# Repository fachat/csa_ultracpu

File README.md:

# Ultra-CPU

Note: this is a part of a larger set of repositories, with [upet_family](https://github.com/fachat/upet_family) as the main repository.

This is the CPU board for a re-incarnation of the Commodore PET or other computer(s) from the later 1970s.

It is build on a Eurocard board and has only parts that can still be obtained new in 2024.
It uses the [CS/A bus interface](http://www.6502.org/users/andre/csa/index.html) to use other I/O boards.

As the memory mapping is programmable using the FPGA on the board, multiple types of computers can
potentially re-created. I started with my favourite one, the Commodore PET.

The reason this board is called Ultra-CPU is because it can potentially be used to recreate not only the Commodore PET.
The downside compared to the Micro-PET is, that it needs a separate I/O board to re-create a Commodore PET.
This can be found [here on my CS/A page](http://www.6502.org/users/andre/csa/petio/index.html).

## Features

The board is built with a number of features:

- Commodore 3032 / 4032 / 8032 / 8296 with options menu to select at boot
  - Boot-menu to select different PET versions to run (BASIC 1, 2, 4)
  - 40 col character display
  - 80 col character display
- Improved system design:
  - 512k video RAM, plus 512k fast RAM, accessible using banks on the W65816 CPU
  - boot from an SPI Flash ROM
  - up to 17.5 MHz mode (via configuration register)
  - Write protection for the PET ROMs once copied to RAM
  - lower 32k RAM mappable from all of the 512k fast RAM
- Improved Video output:
  - VGA color video output (RGBI in 768x576 mode)
  - based on 720x576@60Hz VGA video timing (i.e. including borders at 40/80 columns)
  - modifyable character set
  - 40/80 column display switchable
  - 25/50 rows display switch
  - multiple video pages mappable to $8000 video mem address
  - Mulitple colour modes (Colour-PET, C128 VDC-compatible, Multicolour)
  - Colour Hires (VDC-compatible, Multicolour)
  - 16 colours out of a colour palette of 64 colours displayed simultaneously.
- DAC audio output
  - DMA engine to play audio samples on stereo sound output
- Built-in extra hardware:
  - USB host mode interface (for keyboard / mouse)
  - Real-Time-Clock (battery-buffered)
  - Ethernet/Wifi (via Breakout board)
  - SD-Card (via Breakout board)
- CS/A bus interface
  - multiple options to use bus devices, e.g. in I/O window
  - Together with [Ultra-Bus](https://github.com/fachat/csa_ultrabus) backplane Apple-II and RC2014 devices can be used

## Overview

The system architecture is actually rather simple, as you can see in the following graphics.

The main functionality is "hidden" inside the FPGA. It does:

1. clock generation and management
2. memory mapping
3. video generation.
4. SPI interface and boot

On the CPU side of the FPGA it is actually a rather almost normal 65816 computer, 
with the exception that the bank register (that catches and stores the address lines 
A16-23 from the CPU's data bus) is in the FPGA, and that there is no ROM. The ROM has been
replaced with some code in the FPGA that copies the initial program to the CPU accessible
RAM, taking it from the Flash Boot ROM via SPI. This actually simplifies the design,
as 

1. parallel ROMs are getting harder to come by and
2. they are typically not as fast as is needed, and
3. with the SPI boot they don't occupy valuable CPU address space.

The video generation is done using time-sharing access to the video RAM.
The VGA output is 720x576 at 50Hz. So there is a pixel clock of 27MHz.

The system runs at 13.5MHz, so a byte of pixel output (i.e. eight pixels) has four
memory accesses to VRAM. Two of them are reserved for video access, one for fetching the
character data (e.g. at $08xxx in the PET), and the second one to fetch the "character ROM"
data, i.e. the pixel data for a character. This is also stored in VRAM, and is being loaded
there from the Flash Boot ROM by the initial boot loader.

The FPGA reads the character data, stores it to fetch the character pixel data, and streams
that out using its internal video shift register.

For more detailled descriptions of the features and how to use them, pls see the 
[FPGA repository](https://github.com/fachat/upet_fpga),
as described in the next section.

## Version History

- [Revision 2.1A](https://github.com/fachat/csa_ultracpu/tree/r2.1a): Version using a Spartan 6 FPGA
- [Revision 1.3C](https://github.com/fachat/csa_ultracpu/tree/r1.3c): first working version using a Spartan 3E FPGA
- [Revision 1.2B](https://github.com/fachat/csa_ultracpu/tree/csa_ultracpu_1.2b): Version with CPLD and external colour generation.

## Known Issues

The following issues have been identified:

* Audio quality

Below are the fixes for these. Note, these are NOT yet in the BOM.

### Audio quality

The DAC audio output is not linear with the given schematics. This can be fixed by

* removing R30 and R32
* replace C3 and C10 with a 22uF  electrolytic cap. Orient minus pole to the output connector

## Building

Here are three subdirectories:

- [Board](Board/) That contains the board schematics and layout
- [Demo](Demo/) Some demo programs
- [tests](tests/) Some test programs

- [FPGA code](https://github.com/fachat/upet_fpga) This separate repository contains the VHDL code to program the FPGA logic chip used, and describes the configuration options - including the SPI and DAC usage and the Video feature and register description.
- [ROM](https://github.com/fachat/upet_roms) This separate repository contains the ROM contents to boot

### Board

To build the board, you have to find a provider that builds PCBs from Eagle .brd files.
Additionally, gerber files and a full Bill-of-material are provided in the Board subdirectory.

### FPGA

The FPGA is a Xilinx Spartan 6 programmable logic chip. It runs on 3.3V, 
so the bus interface has to convert between 3.3V and 5V. Compared to previous versions and the Micro-PET, also
the RAM and CPU on this board run on 3.3V now.
The FPGA logic here is programmed in VHDL.

The FPGA programming is actually stored in an SPI Flash Prom, so makes re-creating it even easier compared to 
the previous versions that used a CPLD - the CPLD required a separate programmer, now a (serial) Flash programmer suffices.

### ROM

The ROM image can be built using gcc, xa65, and make. Use your favourite EPROM programmer to burn it into the SPI Flash chip.

The ROM contains images of all required ROM images for BASIC 1, 2, and 4, and corresponding editor ROMs, including
some that have been extended with wedges and colour-PET functionality.

The updated editor ROMs are from [Steve's Editor ROM project](http://www.6502.org/users/sjgray/projects/editrom/index.html) and can handle C64 keyboards, has a DOS wedge included, and resets into the Micro-PET boot menu.

For more details see the [ROM repository](https://github.com/fachat/upet_roms)

## Gallery

### The system

### Graphics feature overview

Note that this version is without the (optional) "Brown Fix" that is included in version 1.0B of the board.

### Board

### Boot menu and OS boot screen

### V1.2 system views

### Debugging during development

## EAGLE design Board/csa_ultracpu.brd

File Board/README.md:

# Board

The board is a two-layer Eurocard, i.e. 160mm x 100mm.

## Schematics & Layout

The schematics and layout have been created with Cadsoft Eagle.
So, here you can find the 

- [csa_ultracpu.sch](csa_ultracpu.sch) and
- [csa_ultracpu.brd](csa_ultracpu.brd) files

But, you can still have a look at the schematics and layout using the
PNG images created

- [csa_ultracpu_v2.0b-sch-1.png](csa_ultracpu_v2.0b-sch-1.png) Part 1 - CS/A Bus interface
- [csa_ultracpu_v2.0b-sch-2.png](csa_ultracpu_v2.0b-sch-2.png) Part 2 - CPLD, CPU, Fast RAM
- [csa_ultracpu_v2.0b-sch-3.png](csa_ultracpu_v2.0b-sch-3.png) Part 3 - Power
- [csa_ultracpu_v2.0b-sch-4.png](csa_ultracpu_v2.0b-sch-4.png) Part 4 - Video and Audio output
- [csa_ultracpu_v2.0b-sch-5.png](csa_ultracpu_v2.0b-sch-5.png) Part 5 - SPI devices (Eth, USB, RTCC, ...)
- [csa_ultracpu_v2.0b-sch-6.png](csa_ultracpu_v2.0b-sch-6.png) Part 6 - Video RAM, data fetch and shift register

- [csa_ultracpu_v2.0b-layout.png](csa_ultracpu_v2.0b-layout.png) layout of the chips
- [csa_ultracpu_v2.0b-brd.png](csa_ultracpu_v2.0b-brd.png) layout of the traces

## Bill of Material

The main chips are:

- 1x W65816S CPU
- 1x x Spartan 6 FPGA
- 2x 8x512k parallel SRAM with 25ns access time
- Several ICs for Video generation
- several ICs for the bus interface
- 1x DS1813 RESET controller

- 70 MHZ crystal oscillator
- 16 MHZ crystal oscillator (bus clock - may be optional)

- Voltage regulators

- bypass caps

- 1x LM2937-3.3V SOT
- div. resistors/caps to generate 3.3V output

More details can be found in the [Eagle parts list](csa_ultracpu.csv).

A full [BOM](csa_ultracpu_BOM.xlsx) with parts numbers from Mouser is now provided as well.

## Changelog

### V2.0B

This moves from the Spartan 3 to a Spartan 6, increases clock speed to 70 MHz for a 
higher resolutoin video output, and more.

### V1.3C

This is a technology change of the programmable logic from the CPLD to an FPGA.
The FPGA has the same footprint, but much more space for logic inside. 
This allowed to integrate proper colour support, bitmaps, sprites, and many more
graphics features. A DAC allows outputting digital sound. 

### V1.0B

This fixes couple of things I found in V1.0A:

- The order of the color/intensity signals was the wrong way around
- The A/B and G inputs of IC15 had been accidently swapped
- An optional second color buffer has been removed as timing was good enough for it not be needed
- An optional "brown fix" has been added.
- On the board, two bypass caps were placed under the CPU socket
- On the board, the JP1 connector has been turned 180 degrees to confirm existing boards

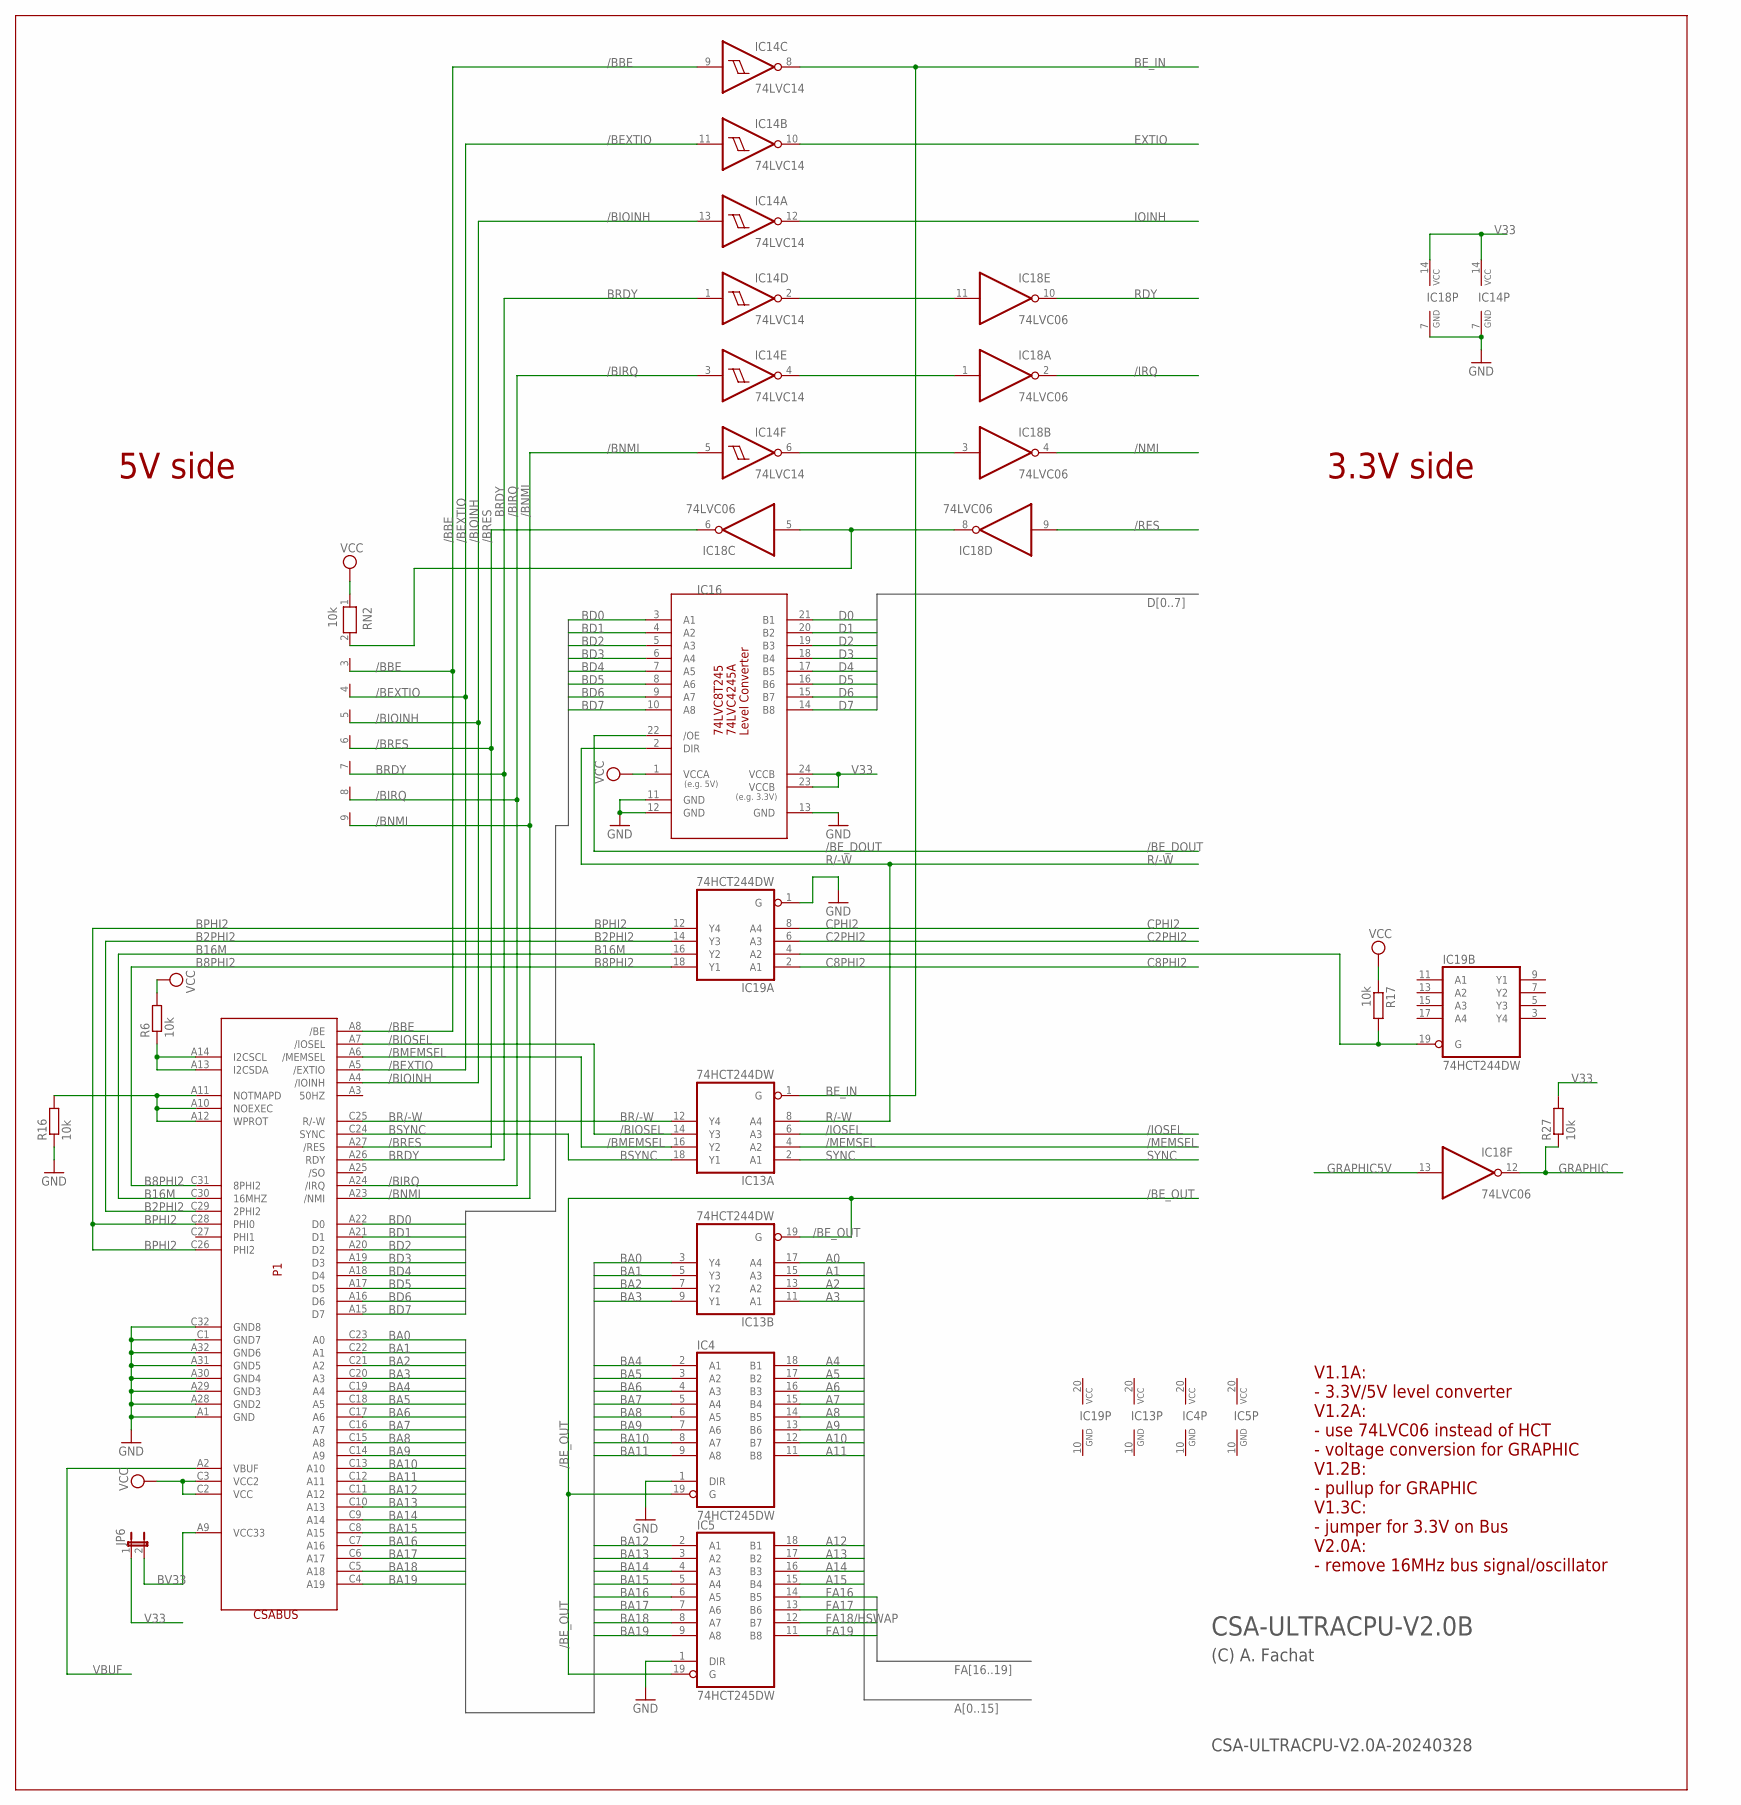
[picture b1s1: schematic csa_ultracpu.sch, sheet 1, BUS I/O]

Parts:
IC4, IC5: 74HCT245DW; SO20W
IC13, IC19: 74HCT244DW; SO20W
IC14: 74LVC14; SO14
IC16: 74LVC8T245SO24; SO24L
IC18: 74LVC06; SO14
JP6: JP1E; JP1
P1: CSABUS
R6, R16, R17, R27: 10k; 0204/5
RN2: 10k; RN-9

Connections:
/BBE: IC14.9 (I), P1.A8 (/BE), RN2.3
/BEXTIO: IC14.11 (I), P1.A5 (/EXTIO), RN2.4
/BE_DOUT: IC16.22 (/OE); also elsewhere on the board
/BE_OUT: IC4.19 (G), IC5.19 (G), IC13.19 (G); also elsewhere on the board
/BIOINH: IC14.13 (I), P1.A4 (/IOINH), RN2.5
/BIOSEL: IC13.14 (Y3), P1.A7 (/IOSEL)
/BIRQ: IC14.3 (I), P1.A24 (/IRQ), RN2.8
/BMEMSEL: IC13.16 (Y2), P1.A6 (/MEMSEL)
/BNMI: IC14.5 (I), P1.A23 (/NMI), RN2.9
/BRES: IC18.6 (O), P1.A27 (/RES), RN2.6
/IOSEL: IC13.6 (A3); also elsewhere on the board
/IRQ: IC18.2 (O); also elsewhere on the board
/MEMSEL: IC13.4 (A2); also elsewhere on the board
/NMI: IC18.4 (O); also elsewhere on the board
/RES: IC18.9 (I); also elsewhere on the board
A0: IC13.17 (A4); also elsewhere on the board
A1: IC13.15 (A3); also elsewhere on the board
A2: IC13.13 (A2); also elsewhere on the board
A3: IC13.11 (A1); also elsewhere on the board
A4: IC4.18 (B1); also elsewhere on the board
A5: IC4.17 (B2); also elsewhere on the board
A6: IC4.16 (B3); also elsewhere on the board
A7: IC4.15 (B4); also elsewhere on the board
A8: IC4.14 (B5); also elsewhere on the board
A9: IC4.13 (B6); also elsewhere on the board
A10: IC4.12 (B7); also elsewhere on the board
A11: IC4.11 (B8); also elsewhere on the board
A12: IC5.18 (B1); also elsewhere on the board
A13: IC5.17 (B2); also elsewhere on the board
A14: IC5.16 (B3); also elsewhere on the board
A15: IC5.15 (B4); also elsewhere on the board
B2PHI2: IC19.14 (Y3), P1.C29 (2PHI2)
B8PHI2: IC19.18 (Y1), P1.C31 (8PHI2)
B16M: IC19.16 (Y2), P1.C30 (16MHZ)
BA0: IC13.3 (Y4), P1.C23 (A0)
BA1: IC13.5 (Y3), P1.C22 (A1)
BA2: IC13.7 (Y2), P1.C21 (A2)
BA3: IC13.9 (Y1), P1.C20 (A3)
BA4: IC4.2 (A1), P1.C19 (A4)
BA5: IC4.3 (A2), P1.C18 (A5)
BA6: IC4.4 (A3), P1.C17 (A6)
BA7: IC4.5 (A4), P1.C16 (A7)
BA8: IC4.6 (A5), P1.C15 (A8)
BA9: IC4.7 (A6), P1.C14 (A9)
BA10: IC4.8 (A7), P1.C13 (A10)
BA11: IC4.9 (A8), P1.C12 (A11)
BA12: IC5.2 (A1), P1.C11 (A12)
BA13: IC5.3 (A2), P1.C10 (A13)
BA14: IC5.4 (A3), P1.C9 (A14)
BA15: IC5.5 (A4), P1.C8 (A15)
BA16: IC5.6 (A5), P1.C7 (A16)
BA17: IC5.7 (A6), P1.C6 (A17)
BA18: IC5.8 (A7), P1.C5 (A18)
BA19: IC5.9 (A8), P1.C4 (A19)
BD0: IC16.3 (A1), P1.A22 (D0)
BD1: IC16.4 (A2), P1.A21 (D1)
BD2: IC16.5 (A3), P1.A20 (D2)
BD3: IC16.6 (A4), P1.A19 (D3)
BD4: IC16.7 (A5), P1.A18 (D4)
BD5: IC16.8 (A6), P1.A17 (D5)
BD6: IC16.9 (A7), P1.A16 (D6)
BD7: IC16.10 (A8), P1.A15 (D7)
BE_IN: IC13.1 (G), IC14.8 (O); also elsewhere on the board
BPHI2: IC19.12 (Y4), P1.C26 (PHI2), P1.C28 (PHI0)
BR/-W: IC13.12 (Y4), P1.C25 (R/-W)
BRDY: IC14.1 (I), P1.A26 (RDY), RN2.7
BSYNC: IC13.18 (Y1), P1.C24 (SYNC)
BV33: JP6.2, P1.A9 (VCC33)
C2PHI2: IC19.6 (A3); also elsewhere on the board
C8PHI2: IC19.2 (A1); also elsewhere on the board
CPHI2: IC19.8 (A4); also elsewhere on the board
D0: IC16.21 (B1); also elsewhere on the board
D1: IC16.20 (B2); also elsewhere on the board
D2: IC16.19 (B3); also elsewhere on the board
D3: IC16.18 (B4); also elsewhere on the board
D4: IC16.17 (B5); also elsewhere on the board
D5: IC16.16 (B6); also elsewhere on the board
D6: IC16.15 (B7); also elsewhere on the board
D7: IC16.14 (B8); also elsewhere on the board
EXTIO: IC14.10 (O); also elsewhere on the board
FA16: IC5.14 (B5); also elsewhere on the board
FA17: IC5.13 (B6); also elsewhere on the board
FA18/HSWAP: IC5.12 (B7); also elsewhere on the board
FA19: IC5.11 (B8); also elsewhere on the board
GND: IC4.1 (DIR), IC4.10 (GND), IC5.1 (DIR), IC5.10 (GND), IC13.10 (GND), IC14.7 (GND), IC16.11 (GND), IC16.12 (GND), IC16.13 (GND), IC18.7 (GND), IC19.1 (G), IC19.10 (GND), P1.A1 (GND), P1.A28 (GND2), P1.A29 (GND3), P1.A30 (GND4), P1.A31 (GND5), P1.A32 (GND6), P1.C1 (GND7), P1.C32 (GND8), R16.1; also elsewhere on the board
GRAPHIC: IC18.12 (O), R27.1; also elsewhere on the board
GRAPHIC5V: IC18.13 (I); also elsewhere on the board
IOINH: IC14.12 (O); also elsewhere on the board
unnamed: IC14.4 (O), IC18.1 (I)
unnamed: IC14.6 (O), IC18.3 (I)
unnamed: IC18.5 (I), IC18.8 (O), RN2.2
unnamed: IC14.2 (O), IC18.11 (I)
unnamed: IC19.4 (A2), IC19.19 (G), R17.2
unnamed: P1.A10 (NOEXEC), P1.A11 (NOTMAPD), P1.A12 (WPROT), R16.2
unnamed: P1.A13 (I2CSDA), P1.A14 (I2CSCL), R6.1
R/-W: IC13.8 (A4), IC16.2 (DIR); also elsewhere on the board
RDY: IC18.10 (O); also elsewhere on the board
SYNC: IC13.2 (A1); also elsewhere on the board
V33: IC14.14 (VCC), IC16.23 (VCCB), IC16.24 (VCCB), IC18.14 (VCC), JP6.1, R27.2; also elsewhere on the board
VBUF: P1.A2 (VBUF); also elsewhere on the board
VCC: IC4.20 (VCC), IC5.20 (VCC), IC13.20 (VCC), IC16.1 (VCCA), IC19.20 (VCC), P1.C2 (VCC), P1.C3 (VCC2), R6.2, R17.1, RN2.1; also elsewhere on the board

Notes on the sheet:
CSA-ULTRACPU-V2.0A-20240328
CSA-ULTRACPU-V2.0B
(C) A. Fachat
3.3V side
5V side
V1.1A: - 3.3V/5V level converter V1.2A: - use 74LVC06 instead of HCT - voltage conversion for GRAPHIC V1.2B: - pullup for GRAPHIC V1.3C: - jumper for 3.3V on Bus V2.0A: - remove 16MHz bus signal/oscillator

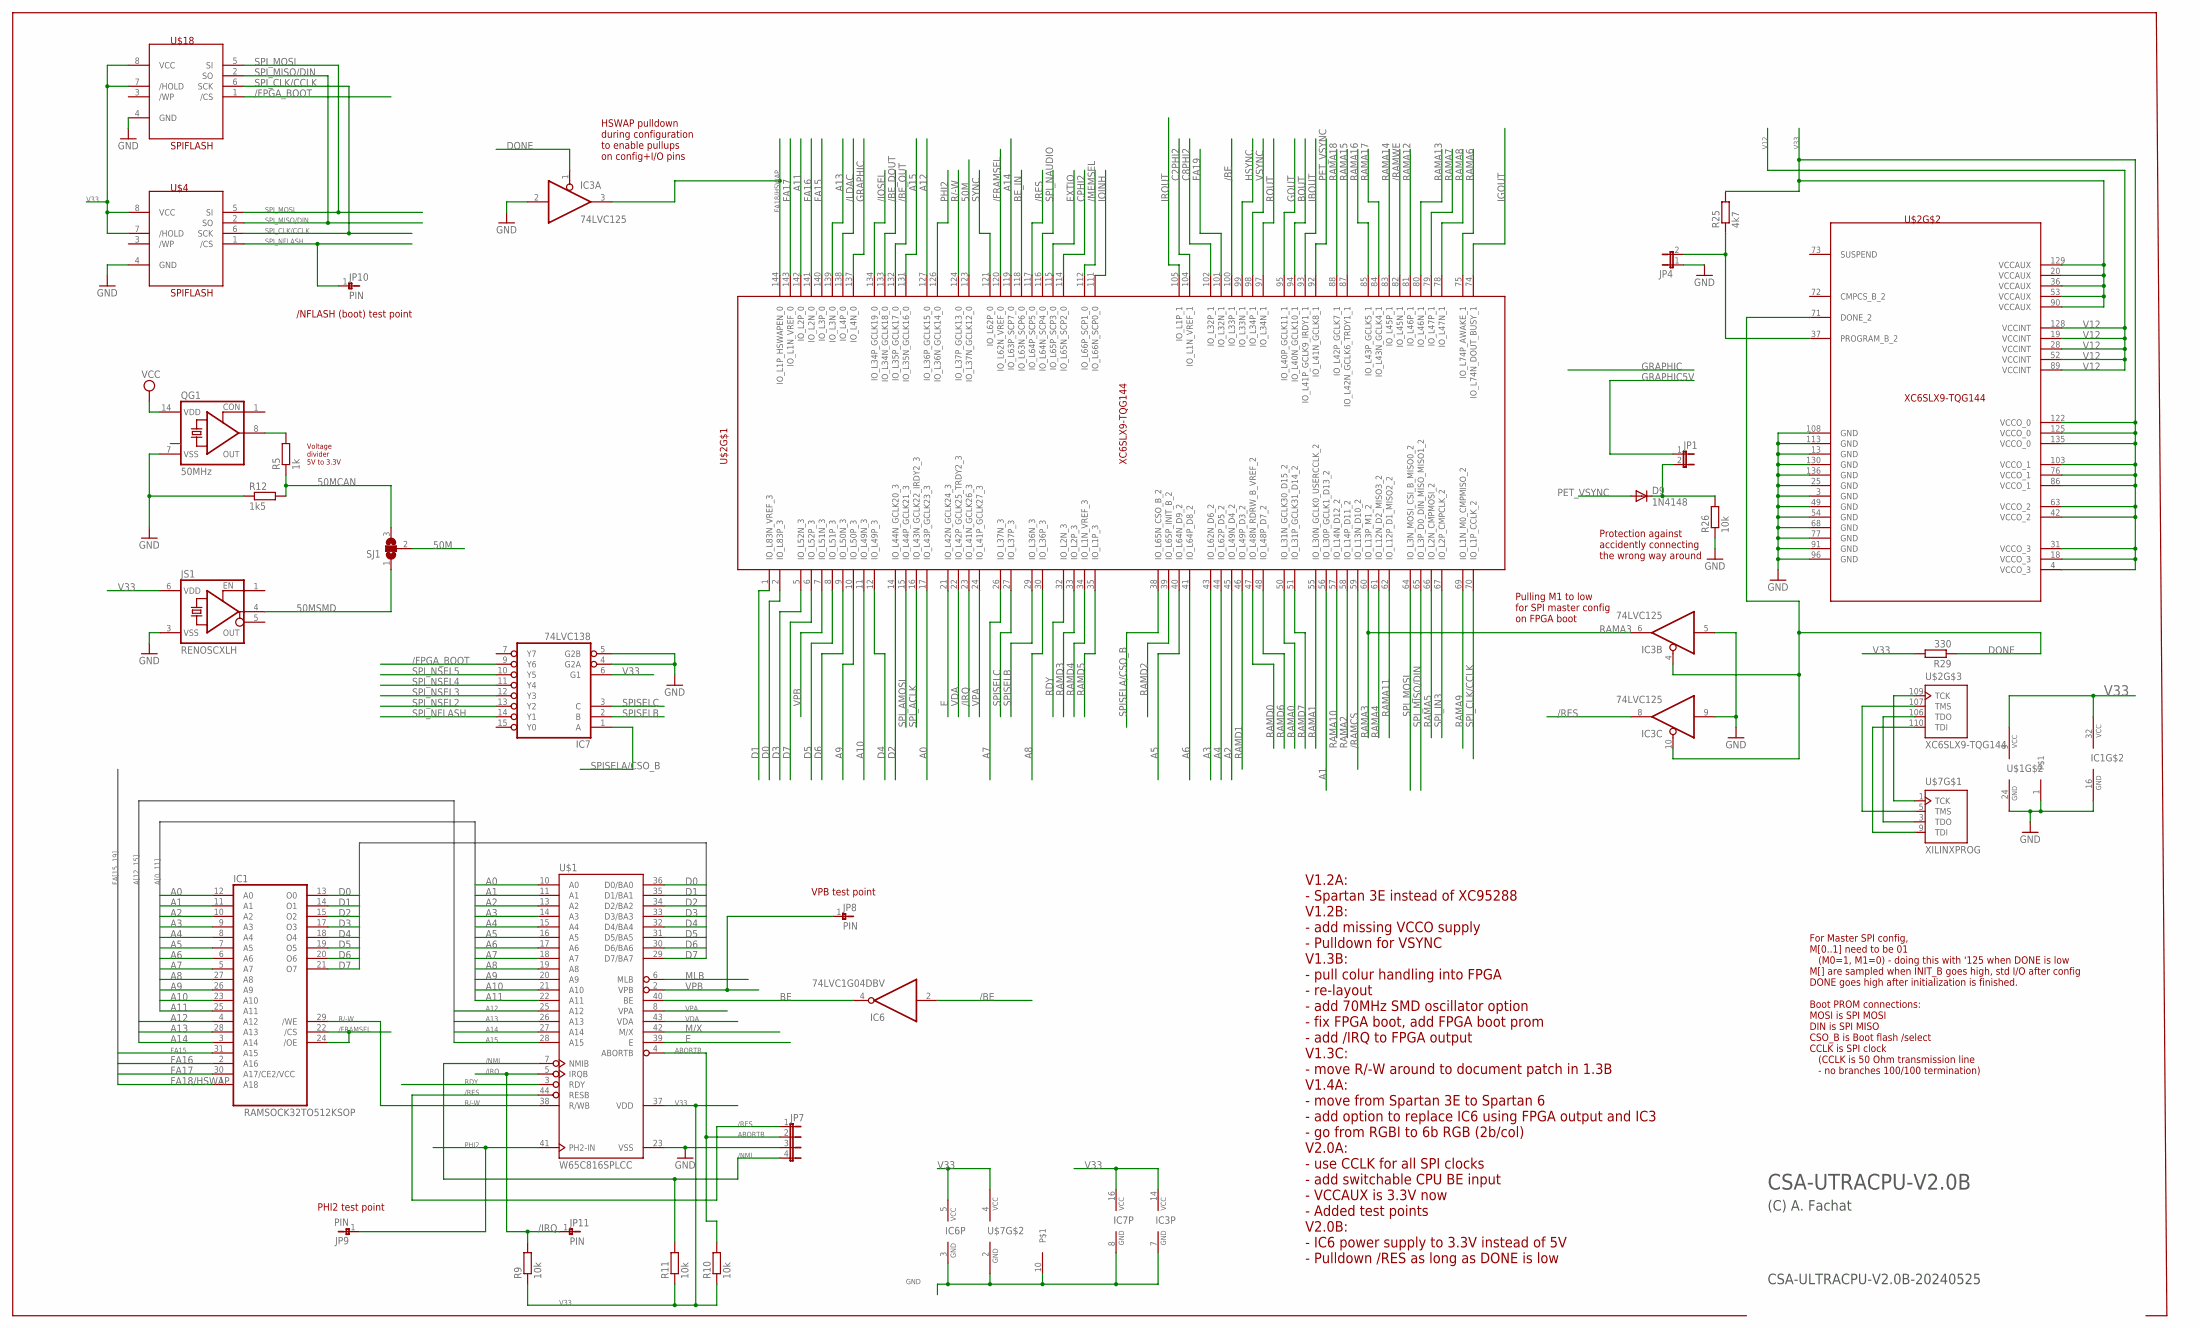
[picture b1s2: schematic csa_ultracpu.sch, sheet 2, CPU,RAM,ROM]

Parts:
D9: 1N4148; D-5
IC1: RAMSOCK32TO512KSOP; SOP32
IC3: 74LVC125; SO14
IC6: 74LVC1G04DBV; SOT23-5
IC7: 74LVC138; SO16
JP1, JP4: JP1E; JP1
JP7: JP4E; JP4
JP8, JP9, JP10, JP11: PIN
JS1: RENOSCXLH; RENJS6
QG1: 50MHz; SG51
R5: 1k; 0207/2V
R9, R10, R11, R26: 10k; 0207/2V
R12: 1k5; 0207/2V
R25: 4k7; 0207/2V
R29: 330; 0207/2V
SJ1: SJ2W; SJ_2
U$1: W65C816SPLCC; PLCC44
U$2: XC6SLX9-TQG144; TQFP144
U$4, U$18: SPIFLASH; DIL08
U$7: XILINXPROG; FLAT10BOX

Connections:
50M: SJ1.2, U$2.123 (IO_L37N_GCLK12_0)
50MCAN: R5.1, R12.2, SJ1.3
50MSMD: JS1.4 (OUT1), SJ1.1
/BE: IC6.2 (I), U$2.100 (IO_L33P_1)
/BE_DOUT: U$2.133 (IO_L34N_GCLK18_0); also elsewhere on the board
/BE_OUT: U$2.132 (IO_L35P_GCLK17_0); also elsewhere on the board
/FPGA_BOOT: IC7.9 (Y6), U$18.1 (/CS)
/FRAMSEL: IC1.22 (/CS), IC1.24 (/OE), U$2.120 (IO_L62N_VREF_0)
/IOSEL: U$2.134 (IO_L34P_GCLK19_0); also elsewhere on the board
/IRQ: JP11.1, R9.2, U$1.5 (IRQB), U$2.23 (IO_L41N_GCLK26_3); also elsewhere on the board
/LDAC: U$2.138 (IO_L4P_0); also elsewhere on the board
/MEMSEL: U$2.112 (IO_L66P_SCP1_0); also elsewhere on the board
/NMI: JP7.4, R11.2, U$1.7 (NMIB); also elsewhere on the board
/RAMCS: U$2.59 (IO_L13N_D10_2); also elsewhere on the board
/RAMWE: U$2.82 (IO_L45N_1); also elsewhere on the board
/RES: IC3.8 (O), JP7.1, U$1.44 (RESB), U$2.117 (IO_L64P_SCP5_0); also elsewhere on the board
A0: IC1.12 (A0), U$1.10 (A0), U$2.17 (IO_L43P_GCLK23_3); also elsewhere on the board
A1: IC1.11 (A1), U$1.11 (A1), U$2.56 (IO_L30P_GCLK1_D13_2); also elsewhere on the board
A2: IC1.10 (A2), U$1.13 (A2), U$2.45 (IO_L49N_D4_2); also elsewhere on the board
A3: IC1.9 (A3), U$1.14 (A3), U$2.43 (IO_L62N_D6_2); also elsewhere on the board
A4: IC1.8 (A4), U$1.15 (A4), U$2.44 (IO_L62P_D5_2); also elsewhere on the board
A5: IC1.7 (A5), U$1.16 (A5), U$2.40 (IO_L64N_D9_2); also elsewhere on the board
A6: IC1.6 (A6), U$1.17 (A6), U$2.41 (IO_L64P_D8_2); also elsewhere on the board
A7: IC1.5 (A7), U$1.18 (A7), U$2.26 (IO_L37N_3); also elsewhere on the board
A8: IC1.27 (A8), U$1.19 (A8), U$2.30 (IO_L36P_3); also elsewhere on the board
A9: IC1.26 (A9), U$1.20 (A9), U$2.10 (IO_L50P_3); also elsewhere on the board
A10: IC1.23 (A10), U$1.21 (A10), U$2.11 (IO_L49N_3); also elsewhere on the board
A11: IC1.25 (A11), U$1.22 (A11), U$2.142 (IO_L2P_0); also elsewhere on the board
A12: IC1.4 (A12), U$1.25 (A12), U$2.127 (IO_L36P_GCLK15_0); also elsewhere on the board
A13: IC1.28 (A13), U$1.26 (A13), U$2.139 (IO_L3N_0); also elsewhere on the board
A14: IC1.3 (A14), U$1.27 (A14), U$2.119 (IO_L63P_SCP7_0); also elsewhere on the board
A15: U$1.28 (A15), U$2.131 (IO_L35N_GCLK16_0); also elsewhere on the board
ABORTB: JP7.2, R10.2, U$1.4 (ABORTB)
BE: IC6.4 (O), U$1.40 (BE)
BE_IN: U$2.118 (IO_L63N_SCP6_0); also elsewhere on the board
BOUT: U$2.94 (IO_L40N_GCLK10_1); also elsewhere on the board
C2PHI2: U$2.104 (IO_L1N_VREF_1); also elsewhere on the board
C8PHI2: U$2.102 (IO_L32P_1); also elsewhere on the board
CPHI2: U$2.114 (IO_L65N_SCP2_0); also elsewhere on the board
D0: IC1.13 (O0), U$1.36 (D0/BA0), U$2.2 (IO_L83P_3); also elsewhere on the board
D1: IC1.14 (O1), U$1.35 (D1/BA1), U$2.1 (IO_L83N_VREF_3); also elsewhere on the board
D2: IC1.15 (O2), U$1.34 (D2/BA2), U$2.14 (IO_L44N_GCLK20_3); also elsewhere on the board
D3: IC1.17 (O3), U$1.33 (D3/BA3), U$2.5 (IO_L52N_3); also elsewhere on the board
D4: IC1.18 (O4), U$1.32 (D4/BA4), U$2.12 (IO_L49P_3); also elsewhere on the board
D5: IC1.19 (O5), U$1.31 (D5/BA5), U$2.8 (IO_L51P_3); also elsewhere on the board
D6: IC1.20 (O6), U$1.30 (D6/BA6), U$2.9 (IO_L50N_3); also elsewhere on the board
D7: IC1.21 (O7), U$1.29 (D7/BA7), U$2.6 (IO_L52P_3); also elsewhere on the board
DONE: IC3.1 (OE), IC3.4 (OE), IC3.10 (OE), R29.1, U$2.71 (DONE_2)
E: U$1.39 (E), U$2.21 (IO_L42N_GCLK24_3)
EXTIO: U$2.115 (IO_L65P_SCP3_0); also elsewhere on the board
FA15: IC1.31 (A15), U$2.140 (IO_L3P_0)
FA16: IC1.2 (A16), U$2.141 (IO_L2N_0); also elsewhere on the board
FA17: IC1.30 (A17/CE2/VCC), U$2.143 (IO_L1N_VREF_0); also elsewhere on the board
FA18/HSWAP: IC1.1 (A18), IC3.3 (O), U$2.144 (IO_L1P_HSWAPEN_0); also elsewhere on the board
FA19: U$2.101 (IO_L32N_1); also elsewhere on the board
GND: IC1.16 (GND), IC3.2 (I), IC3.5 (I), IC3.7 (GND), IC3.9 (I), IC6.3 (GND), IC7.4 (G2A), IC7.5 (G2B), IC7.8 (GND), JP4.1, JP7.3, JS1.3 (VSS), QG1.7 (VSS), R12.1, R26.1, U$1.1, U$1.23 (VSS), U$1.24 (GND), U$2.3 (GND), U$2.13 (GND), U$2.25 (GND), U$2.49 (GND), U$2.54 (GND), U$2.68 (GND), U$2.77 (GND), U$2.91 (GND), U$2.96 (GND), U$2.108 (GND), U$2.113 (GND), U$2.130 (GND), U$2.136 (GND), U$4.4 (GND), U$7.2 (GND), U$7.10, U$18.4 (GND); also elsewhere on the board
GOUT: U$2.95 (IO_L40P_GCLK11_1); also elsewhere on the board
GRAPHIC: U$2.137 (IO_L4N_0); also elsewhere on the board
GRAPHIC5V: JP1.1; also elsewhere on the board
HSYNC: U$2.99 (IO_L33N_1); also elsewhere on the board
IBOUT: U$2.93 (IO_L41P_GCLK9_IRDY1_1); also elsewhere on the board
IGOUT: U$2.74 (IO_L74N_DOUT_BUSY_1); also elsewhere on the board
IOINH: U$2.111 (IO_L66N_SCP0_0); also elsewhere on the board
IROUT: U$2.105 (IO_L1P_1); also elsewhere on the board
M/X: U$1.42 (M/X)
MLB: U$1.6 (MLB)
unnamed: QG1.8 (OUT), R5.2
unnamed: D9.C, JP1.2, R26.2
PET_VSYNC: D9.A, U$2.92 (IO_L41N_GCLK8_1)
PHI2: JP9.1, U$1.41 (PH2-IN), U$2.126 (IO_L36N_GCLK14_0)
PROG_B: JP4.2, R25.1, U$2.37 (PROGRAM_B_2)
R/-W: IC1.29 (/WE), U$1.38 (R/WB), U$2.124 (IO_L37P_GCLK13_0); also elsewhere on the board
RAMA0: U$2.50 (IO_L31N_GCLK30_D15_2); also elsewhere on the board
RAMA1: U$2.55 (IO_L30N_GCLK0_USERCCLK_2); also elsewhere on the board
RAMA2: U$2.58 (IO_L14P_D11_2); also elsewhere on the board
RAMA3: IC3.6 (O), U$2.60 (IO_L13P_M1_2); also elsewhere on the board
RAMA4: U$2.61 (IO_L12N_D2_MISO3_2); also elsewhere on the board
RAMA5: U$2.66 (IO_L2N_CMPMOSI_2); also elsewhere on the board
RAMA6: U$2.75 (IO_L74P_AWAKE_1); also elsewhere on the board
RAMA7: U$2.79 (IO_L47P_1); also elsewhere on the board
RAMA8: U$2.78 (IO_L47N_1); also elsewhere on the board
RAMA9: U$2.69 (IO_L1N_M0_CMPMISO_2); also elsewhere on the board
RAMA10: U$2.57 (IO_L14N_D12_2); also elsewhere on the board
RAMA11: U$2.62 (IO_L12P_D1_MISO2_2); also elsewhere on the board
RAMA12: U$2.81 (IO_L46P_1); also elsewhere on the board
RAMA13: U$2.80 (IO_L46N_1); also elsewhere on the board
RAMA14: U$2.83 (IO_L45P_1); also elsewhere on the board
RAMA15: U$2.87 (IO_L42N_GCLK6_TRDY1_1); also elsewhere on the board
RAMA16: U$2.85 (IO_L43P_GCLK5_1); also elsewhere on the board
RAMA17: U$2.84 (IO_L43N_GCLK4_1); also elsewhere on the board
RAMA18: U$2.88 (IO_L42P_GCLK7_1); also elsewhere on the board
RAMD0: U$2.47 (IO_L48N_RDRW_B_VREF_2); also elsewhere on the board
RAMD1: U$2.46 (IO_L49P_D3_2); also elsewhere on the board
RAMD2: U$2.39 (IO_L65P_INIT_B_2); also elsewhere on the board
RAMD3: U$2.33 (IO_L2P_3); also elsewhere on the board
RAMD4: U$2.34 (IO_L1N_VREF_3); also elsewhere on the board
RAMD5: U$2.35 (IO_L1P_3); also elsewhere on the board
RAMD6: U$2.48 (IO_L48P_D7_2); also elsewhere on the board
RAMD7: U$2.51 (IO_L31P_GCLK31_D14_2); also elsewhere on the board
RDY: U$1.3 (RDY), U$2.32 (IO_L2N_3); also elsewhere on the board
ROUT: U$2.97 (IO_L34N_1); also elsewhere on the board
SPISELA/CSO_B: IC7.1 (A), U$2.38 (IO_L65N_CSO_B_2)
SPISELB: IC7.2 (B), U$2.29 (IO_L36N_3)
SPISELC: IC7.3 (C), U$2.27 (IO_L37P_3)
SPI_ACLK: U$2.16 (IO_L43N_GCLK22_IRDY2_3); also elsewhere on the board
SPI_AMOSI: U$2.15 (IO_L44P_GCLK21_3); also elsewhere on the board
SPI_CLK/CCLK: U$2.70 (IO_L1P_CCLK_2), U$4.6 (SCK), U$18.6 (SCK); also elsewhere on the board
SPI_IN3: U$2.67 (IO_L2P_CMPCLK_2); also elsewhere on the board
SPI_MISO/DIN: U$2.65 (IO_L3P_D0_DIN_MISO_MISO1_2), U$4.2 (SO), U$18.2 (SO); also elsewhere on the board
SPI_MOSI: U$2.64 (IO_L3N_MOSI_CSI_B_MISO0_2), U$4.5 (SI), U$18.5 (SI); also elsewhere on the board
SPI_NAUDIO: U$2.116 (IO_L64N_SCP4_0); also elsewhere on the board
SPI_NFLASH: IC7.14 (Y1), JP10.1, U$4.1 (/CS)
SPI_NSEL2: IC7.13 (Y2); also elsewhere on the board
SPI_NSEL3: IC7.12 (Y3); also elsewhere on the board
SPI_NSEL4: IC7.11 (Y4); also elsewhere on the board
SPI_NSEL5: IC7.10 (Y5); also elsewhere on the board
SYNC: U$2.121 (IO_L62P_0); also elsewhere on the board
TCK: U$2.109 (TCK), U$7.1 (TCK)
TDI: U$2.110 (TDI), U$7.9 (TDI)
TDO: U$2.106 (TDO), U$7.3 (TDO)
TMS: U$2.107 (TMS), U$7.5 (TMS)
V12: U$2.19 (VCCINT), U$2.28 (VCCINT), U$2.52 (VCCINT), U$2.89 (VCCINT), U$2.128 (VCCINT); also elsewhere on the board
V33: IC1.32 (VCC), IC3.14 (VCC), IC6.5 (VCC), IC7.6 (G1), IC7.16 (VCC), JS1.6 (VDD), R9.1, R10.1, R11.1, R25.2, R29.2, U$1.9 (VCC), U$1.37 (VDD), U$2.4 (VCCO_3), U$2.18 (VCCO_3), U$2.20 (VCCAUX), U$2.31 (VCCO_3), U$2.36 (VCCAUX), U$2.42 (VCCO_2), U$2.53 (VCCAUX), U$2.63 (VCCO_2), U$2.76 (VCCO_1), U$2.86 (VCCO_1), U$2.90 (VCCAUX), U$2.103 (VCCO_1), U$2.122 (VCCO_0), U$2.125 (VCCO_0), U$2.129 (VCCAUX), U$2.135 (VCCO_0), U$4.7 (/HOLD), U$4.8 (VCC), U$7.4 (VCC), U$18.7 (/HOLD), U$18.8 (VCC); also elsewhere on the board
VCC: QG1.14 (VDD); also elsewhere on the board
VDA: U$1.43 (VDA), U$2.22 (IO_L42P_GCLK25_TRDY2_3)
VPA: U$1.8 (VPA), U$2.24 (IO_L41P_GCLK27_3)
VPB: JP8.1, U$1.2 (VPB), U$2.7 (IO_L51N_3)
VSYNC: U$2.98 (IO_L34P_1); also elsewhere on the board

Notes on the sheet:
CSA-ULTRACPU-V2.0B-20240525
CSA-UTRACPU-V2.0B
(C) A. Fachat
V1.2A: - Spartan 3E instead of XC95288 V1.2B: - add missing VCCO supply - Pulldown for VSYNC V1.3B: - pull colur handling into FPGA - re-layout - add 70MHz SMD oscillator option - fix FPGA boot, add FPGA boot prom - add /IRQ to FPGA output V1.3C: - move R/-W around to document patch in 1.3B V1.4A: 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
Voltage divider 5V to 3.3V
Protection against accidently connecting the wrong way around
For Master SPI config, M[0..1] need to be 01 (M0=1, M1=0) - doing this with '125 when DONE is low M[] are sampled when INIT_B goes high, std I/O after config DONE goes high after initialization is finished. Boot PROM connections: MOSI is SPI MOSI DIN is SPI MISO CSO_B is Boot flash /select CCLK is 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
HSWAP pulldown during configuration to enable pullups on config+I/O pins
Pulling M1 to low for SPI master config on FPGA boot
VPB test point
PHI2 test point
/NFLASH (boot) test point

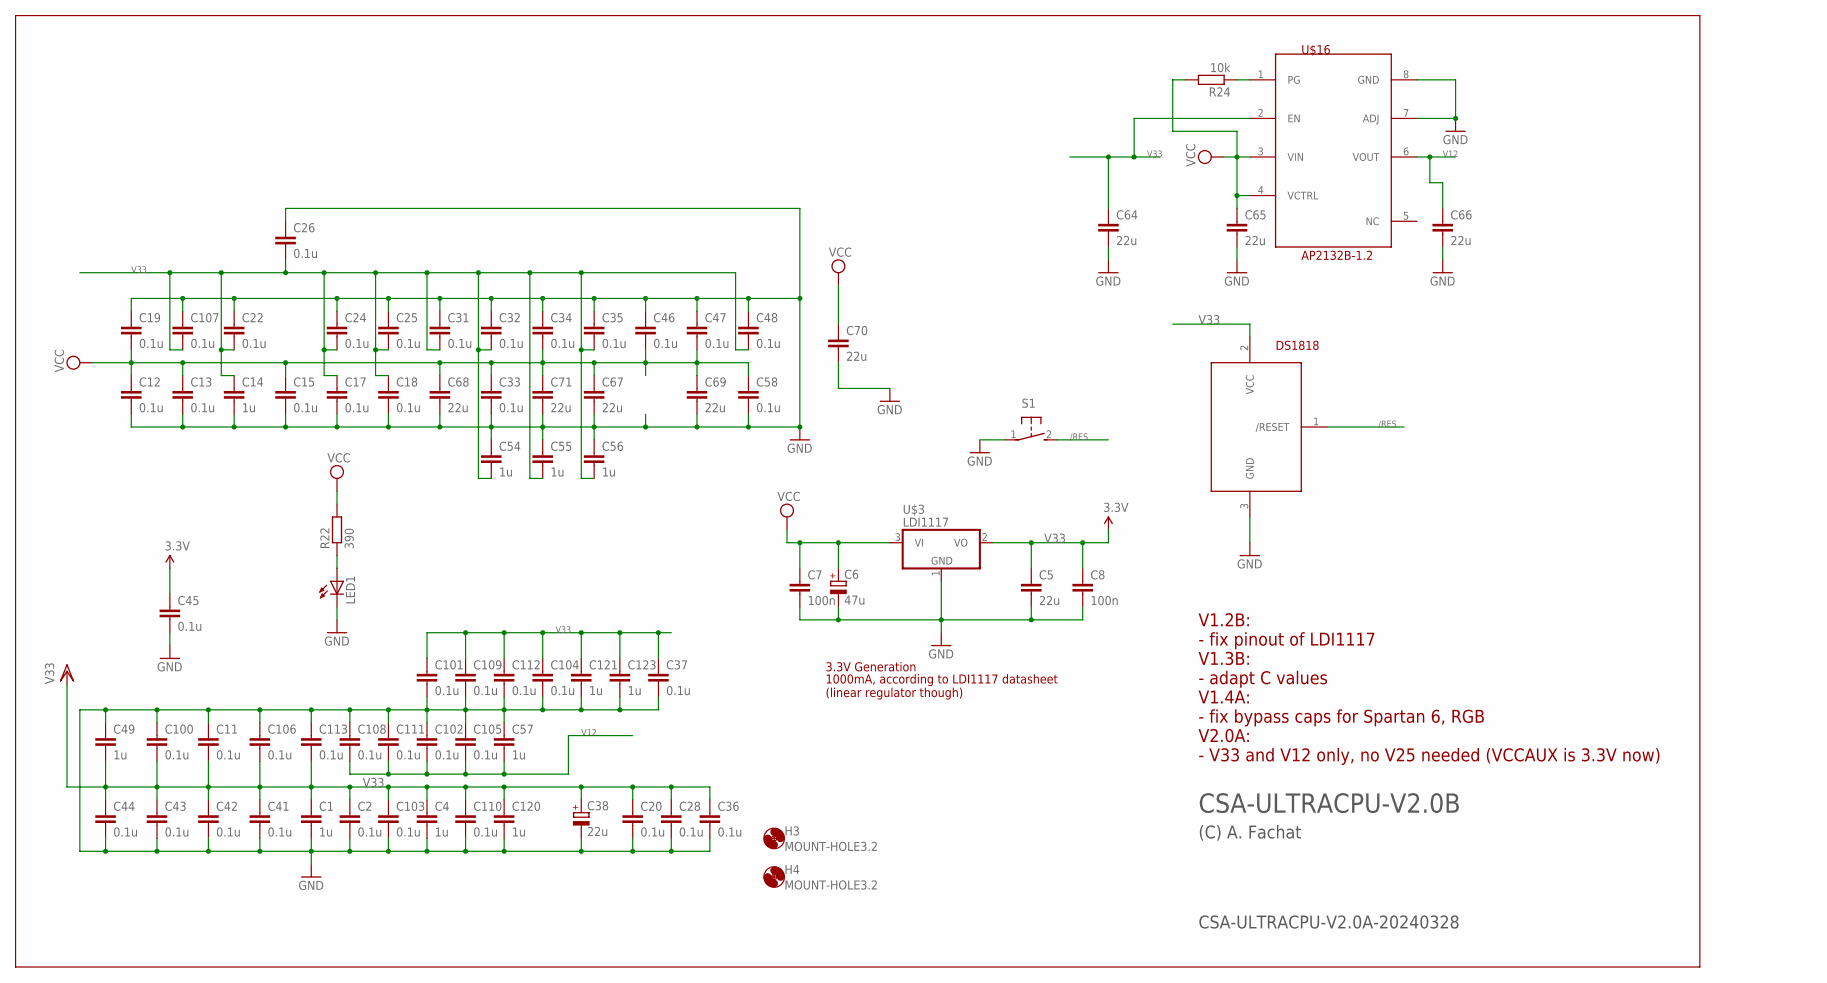
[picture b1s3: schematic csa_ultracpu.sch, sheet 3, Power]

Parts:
C1, C4, C14, C49, C54, C55, C56, C57, C120, C121, C123: 1u; C0603
C2, C11, C12, C13, C15, C17, C18, C19, C20, C22, C24, C25, C26, C28, C31, C32, C33, C34, C35, C36, C37, C41, C42, C43, C44, C45, C46, C47, C48, C58, C100, C101, C102, C103, C104, C105, C106, C107, C108, C109, C110, C111, C112, C113: 0.1u; C0603
C5, C64, C65, C66, C67, C68, C69, C70, C71: 22u; C0805
C6: 47u; E2,5-6
C7, C8: 100n; C0603
C38: 22u; E2,5-6
DS1818: DS1818; TO92
H3, H4: MOUNT-HOLE3.2; 3,2
LED1: LED3MM
R22: 390; 0207/2V
R24: 10k; 0207/2V
S1: 31-XX; B3F-31XX
U$3: LDI1117; SOT223
U$16: AP2132B-1.2; PSOP-8-FIXED

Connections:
/RES: DS1818.1 (/RESET), S1.2 (S); also elsewhere on the board
GND: C1.2, C2.2, C4.2, C5.2, C6.-, C7.2, C8.2, C11.1, C12.2, C13.2, C14.2, C15.2, C17.2, C18.2, C19.1, C20.2, C22.1, C24.1, C25.1, C26.1, C28.2, C31.1, C32.1, C33.2, C34.1, C35.1, C36.2, C37.2, C38.-, C41.2, C42.2, C43.2, C44.2, C45.2, C46.1, C47.1, C48.1, C49.1, C54.1, C55.1, C56.1, C57.1, C58.2, C64.2, C65.2, C66.2, C67.2, C68.2, C69.2, C70.2, C71.2, C100.1, C101.2, C102.1, C103.2, C104.2, C105.1, C106.1, C107.1, C108.1, C109.2, C110.2, C111.1, C112.2, C113.1, C120.2, C121.2, C123.2, DS1818.3 (GND), LED1.K (C), S1.1, U$3.1 (GND), U$16.7 (ADJ), U$16.8 (GND); also elsewhere on the board
unnamed: R24.1, U$16.1 (PG)
unnamed: LED1.A, R22.1
V12: C57.2, C66.1, C102.2, C105.2, C108.2, C111.2, U$16.6 (VOUT); also elsewhere on the board
V33: C1.1, C2.1, C4.1, C5.1, C8.1, C11.2, C14.1, C17.1, C18.1, C20.1, C22.2, C24.2, C25.2, C26.2, C28.1, C31.2, C32.2, C35.2, C36.1, C37.1, C38.+, C41.1, C42.1, C43.1, C44.1, C45.1, C48.2, C49.2, C54.2, C55.2, C56.2, C64.1, C100.2, C101.1, C103.1, C104.1, C106.2, C107.2, C109.1, C110.1, C112.1, C113.2, C120.1, C121.1, C123.1, DS1818.2 (VCC), U$3.2 (VO), U$16.2 (EN); also elsewhere on the board
VCC: C6.+, C7.1, C12.1, C13.1, C15.1, C19.2, C33.1, C34.2, C46.2, C47.2, C58.1, C65.1, C67.1, C68.1, C69.1, C70.1, C71.1, R22.2, R24.2, U$3.3 (VI), U$16.3 (VIN), U$16.4 (VCTRL); also elsewhere on the board

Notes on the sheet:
CSA-ULTRACPU-V2.0A-20240328
CSA-ULTRACPU-V2.0B
(C) A. Fachat
3.3V Generation
1000mA, according to LDI1117 datasheet (linear regulator though)
DS1818
V1.2B: - fix pinout of LDI1117 V1.3B: - adapt C values V1.4A: - fix bypass caps for Spartan 6, RGB V2.0A: - V33 and V12 only, no V25 needed (VCCAUX is 3.3V now)

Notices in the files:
Board/csa_ultracpu.brd:
(C) 2021,2024
